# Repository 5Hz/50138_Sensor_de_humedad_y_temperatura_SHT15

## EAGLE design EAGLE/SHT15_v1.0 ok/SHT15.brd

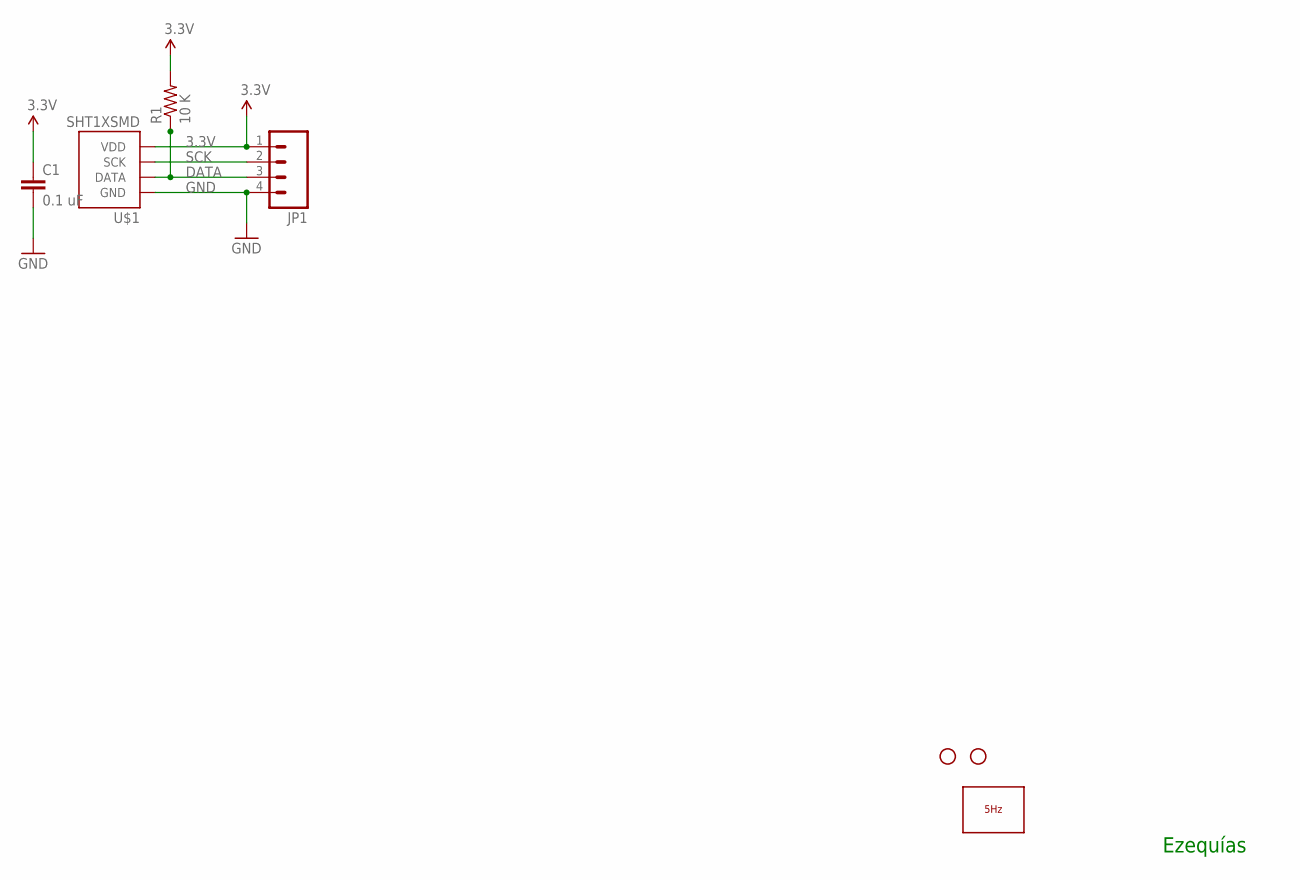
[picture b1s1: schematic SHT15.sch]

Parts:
C1: 0.1 uF; 0603-CAP
JP1: M04PTH; 1X04
JP2, JP3: STAND-OFF
LOGO1: LOGO_5HZ_H_10MM; 5HZ_LOGO_H_10MM
R1: 10 K; 0603-RES
U$1: SHT1XSMD; SHT1X

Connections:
3.3V: C1.1, JP1.1, R1.2, U$1.4 (VDD)
DATA: JP1.3, R1.1, U$1.2 (DATA)
GND: C1.2, JP1.4, U$1.1 (GND)
SCK: JP1.2, U$1.3 (SCK)

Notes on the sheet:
Ezequías

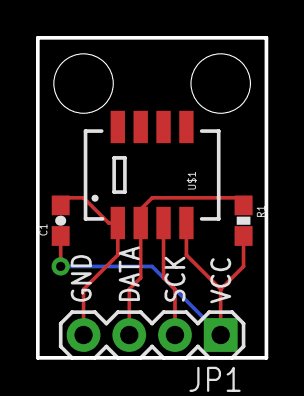
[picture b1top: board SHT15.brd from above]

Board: 2 copper layers, 12.7 x 17.8 mm, 7 parts (1 on the bottom side), 4 nets.

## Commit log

2014-01-14 creación

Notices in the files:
parts and their libraries:
SparkFun: Licensing: CC v3.0 Share-Alike You are welcome to use this library for commercial purposes.
